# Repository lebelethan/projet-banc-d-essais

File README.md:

# Mini projet - banc d'essais - Lebel Ethan

Ce dépot est composé des différents fichiers composant le mini projet de création d'un banc d'essais (pcb et cetera...)
A noter, le fichier SimulIde ne contient que le fichier de code arduino à cause d'une erreur avec ma clé USB.

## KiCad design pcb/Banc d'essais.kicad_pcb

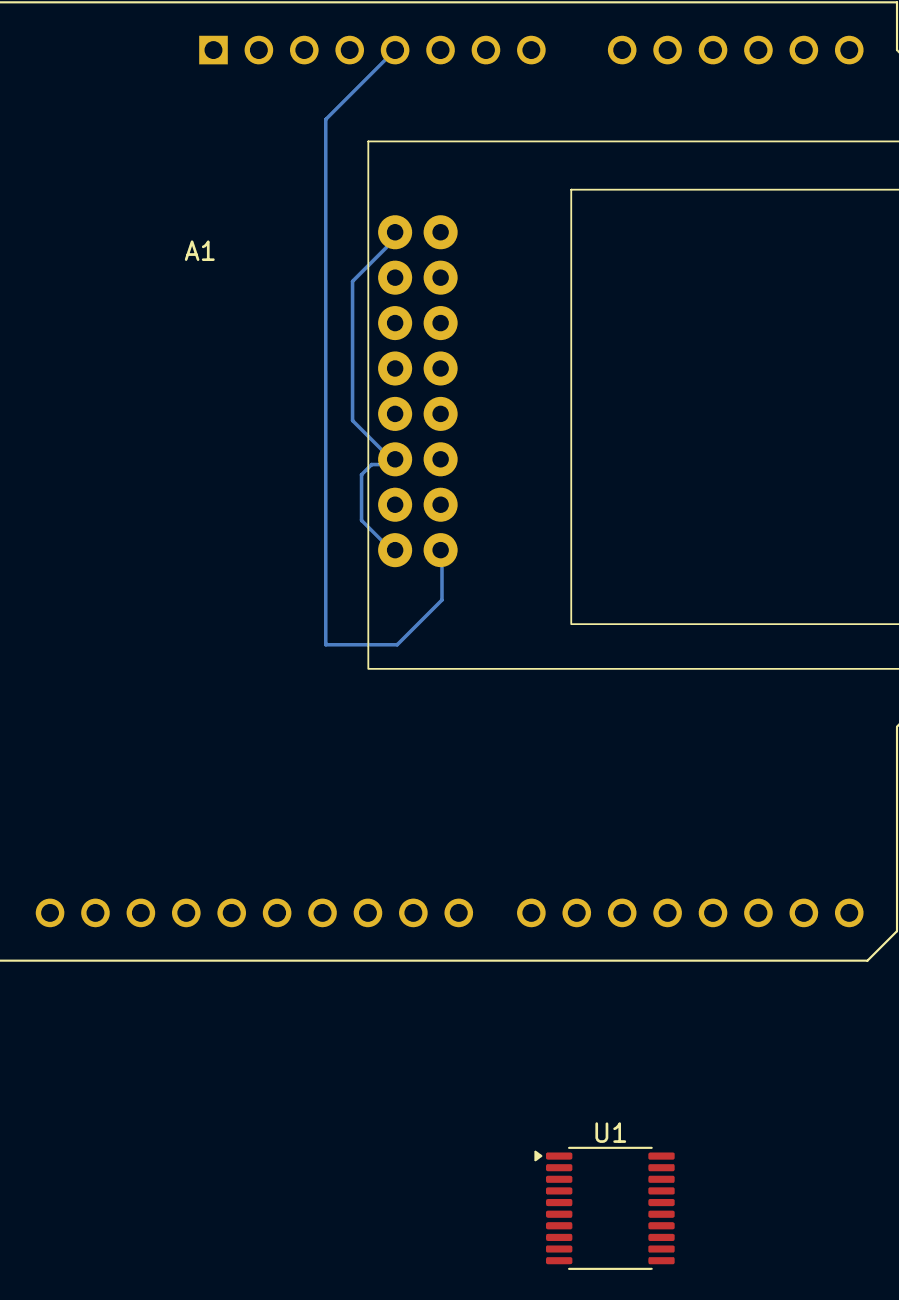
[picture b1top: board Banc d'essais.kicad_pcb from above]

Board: 2 copper layers, 3 parts (0 on the bottom side), 3 nets.

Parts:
A1: Arduino_UNO_R3
Ecran1: Sans titre
U1: MCP4431-xxxx-ST; TSSOP-20_4.4x6.5mm_P0.65mm

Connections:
unnamed: A1.5 (+5V), Ecran1.1 (VDD), U1.11 (P0A)
unnamed: Ecran1.2 (VSS), Ecran1.5 (R/W), Ecran1.16 (K), U1.13 (P0B)
unnamed: Ecran1.3 (V0), U1.12 (P0W)
